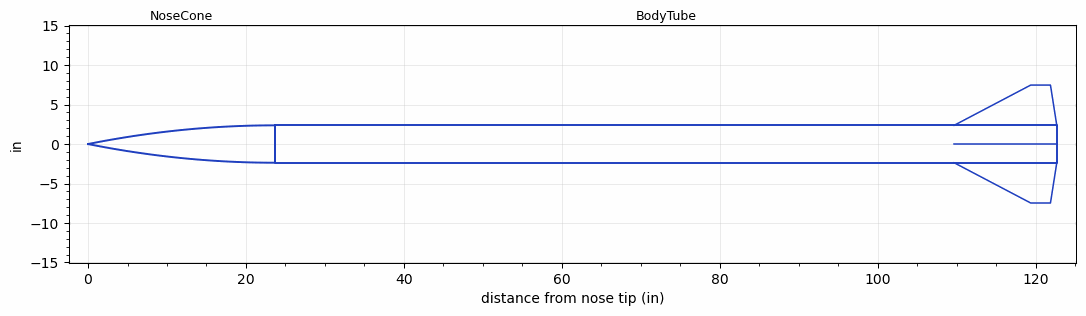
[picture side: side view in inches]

<RASAeroDocument>
 <FileVersion>2</FileVersion>
 <RocketDesign>
  <NoseCone>
   <Length>23.675</Length>
   <Diameter>4.735</Diameter>
   <Shape>Parabolic</Shape>
   <Location>0</Location>
  </NoseCone>
  <BodyTube>
   <Length>99</Length>
   <Diameter>4.735</Diameter>
   <Location>23.675</Location>
   <Fin>
    <Count>4</Count>
    <Chord>13</Chord>
    <Span>5.1</Span>
    <SweepDistance>9.7</SweepDistance>
    <TipChord>2.5</TipChord>
    <Thickness>0.25</Thickness>
    <Location>13</Location>
    <AirfoilSection>Square</AirfoilSection>
   </Fin>
  </BodyTube>
  <Surface>Smooth (Zero Roughness)</Surface>
  <ModifiedBarrowman>False</ModifiedBarrowman>
  <Turbulence>False</Turbulence>
  <UseBooster1>False</UseBooster1>
  <UseBooster2>False</UseBooster2>
 </RocketDesign>
 <LaunchSite>
  <Altitude>0</Altitude>
  <Pressure>0</Pressure>
  <RodAngle>0</RodAngle>
  <RodLength>4</RodLength>
  <Temperature>74</Temperature>
  <WindSpeed>0</WindSpeed>
 </LaunchSite>
 <Recovery>
  <Altitude1>1000</Altitude1>
  <Altitude2>1000</Altitude2>
  <DeviceType1>None</DeviceType1>
  <DeviceType2>None</DeviceType2>
  <Event1>False</Event1>
  <Event2>False</Event2>
  <Size1>1</Size1>
  <Size2>1</Size2>
  <EventType1>None</EventType1>
  <EventType2>None</EventType2>
  <CD1>1.33</CD1>
  <CD2>1.33</CD2>
 </Recovery>
 <SimulationList>
  <Simulation>
   <SustainerEngine>N5800-CS  (CTI)</SustainerEngine>
   <SustainerLaunchWt>60.42</SustainerLaunchWt>
   <SustainerCG>82.28</SustainerCG>
   <SustainerIgnitionDelay>0</SustainerIgnitionDelay>
   <Booster1SeparationDelay>0</Booster1SeparationDelay>
   <Booster1IgnitionDelay>0</Booster1IgnitionDelay>
   <IncludeBooster1>False</IncludeBooster1>
   <Booster2Delay>0</Booster2Delay>
   <IncludeBooster2>False</IncludeBooster2>
   <TimetoApogee>32.29059</TimetoApogee>
   <MaxAltitude>23235.11</MaxAltitude>
   <MaxVelocity>2277.413</MaxVelocity>
  </Simulation>
 </SimulationList>
</RASAeroDocument>
